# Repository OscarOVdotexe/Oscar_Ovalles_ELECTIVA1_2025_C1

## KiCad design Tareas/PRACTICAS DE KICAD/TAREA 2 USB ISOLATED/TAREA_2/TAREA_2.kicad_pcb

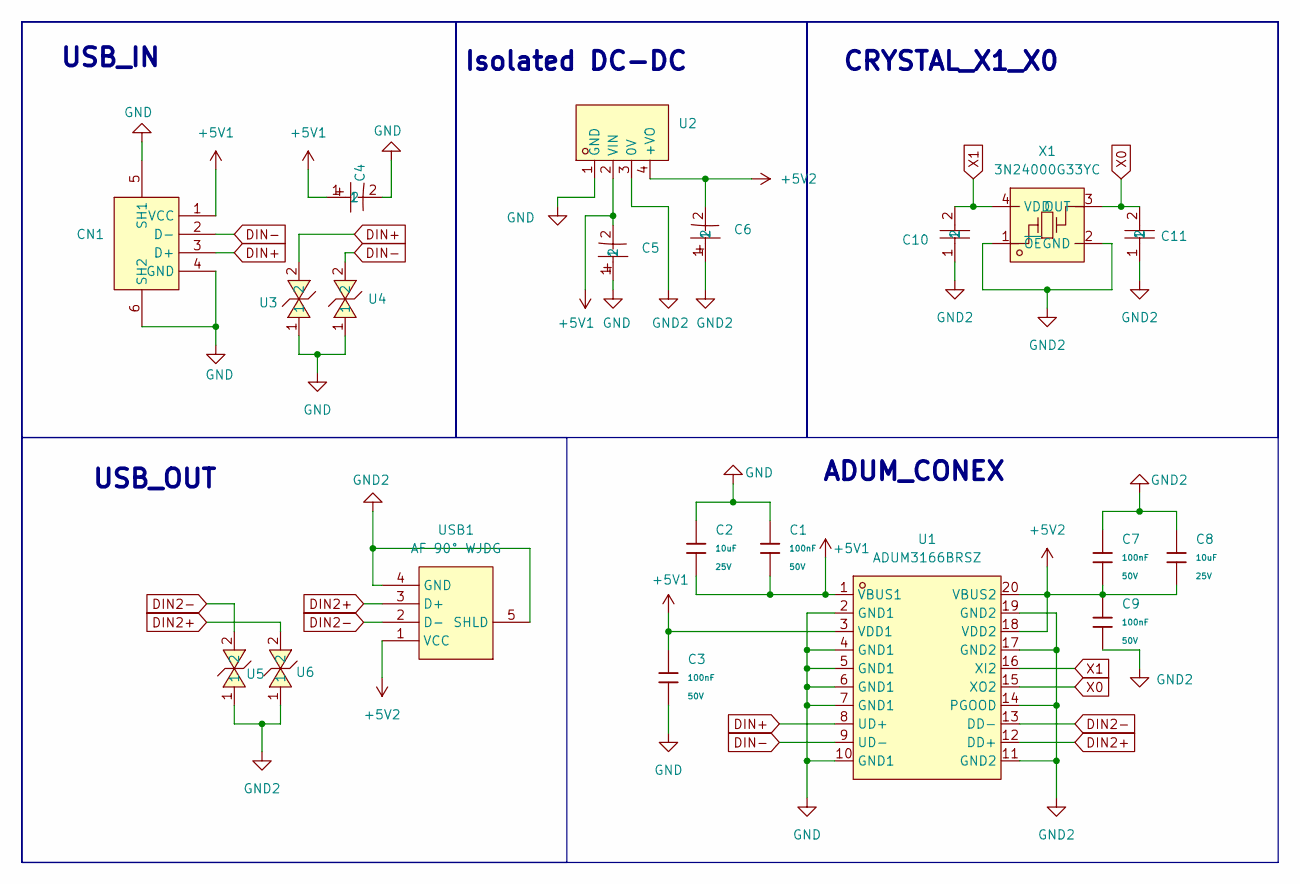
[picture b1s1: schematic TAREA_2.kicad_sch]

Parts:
C1, C3, C7, C9: 100nF; C_0603; Voltage Rated 50V; Tolerance ±10%; Part CC0603KRX7R9BB104; LCSC C14663
C2, C8: 10uF; C_0805; Voltage Rated 25V; Tolerance ±10%; Part CL21A106KAYNNNE; LCSC C15850
C4, C5, C6: 4.7uF 25V 3*5; CAP-TH_BD4.0-P1.50-D0.8-FD; LCSC Part C44582
C10, C11: 0805CG8R0C500NT; C0805; LCSC Part C1839
CN1: USB-B-Female-90; USB-B_TH_USB-B-FEMALE-90; LCSC Part C46392
U1: ADUM3166BRSZ; SSOP-20_L7.2-W5.3-P0.65-LS7.8-BL; LCSC Part C7453661
U2: B0503S-1WR3_C5444000; PWRM-TH_B0503S-1WR2; LCSC Part C5444000
U3, U4, U5, U6: TVSS5VCES-02GP-J_C7473318; SOD-523_L1.2-W0.8-LS1.6-BI; LCSC Part C7473318
USB1: AF 90° WJDG; USB-A-TH_AF-WJDG; LCSC Part C456018
X1: 3N24000G33YC; OSC-SMD_4P-L3.2-W2.5-BL; LCSC Part C252339

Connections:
+5V1: C1.1, C2.2, C3.2, C4.1, C5.2, CN1.1 (VCC), U1.1 (VBUS1), U1.3 (VDD1), U2.2 (VIN)
+5V2: C6.2, C7.1, C8.2, C9.2, U1.18 (VDD2), U1.20 (VBUS2), U2.4 (+VO), USB1.1 (VCC)
DIN2+: U1.12 (DD+), U6.2, USB1.3 (D+)
DIN2-: U1.13 (DD−), U5.2, USB1.2 (D-)
DIN+: CN1.3 (D+), U1.8 (UD+), U3.2
DIN-: CN1.2 (D-), U1.9 (UD−), U4.2
GND: C1.2, C2.1, C3.1, C4.2, C5.1, CN1.4 (GND), CN1.5 (SH1), CN1.6 (SH2), U1.2 (GND1), U1.4 (GND1), U1.5 (GND1), U1.6 (GND1), U1.7 (GND1), U1.10 (GND1), U2.1 (GND), U3.1, U4.1
GND2: C6.1, C7.2, C8.1, C9.1, C10.1, C11.1, U1.11 (GND2), U1.14 (PGOOD), U1.17 (GND2), U1.19 (GND2), U2.3 (0V), U5.1, U6.1, USB1.4 (GND), USB1.5 (SHLD), X1.1 (~OE), X1.2 (GND)
X0: C11.2, U1.15 (XO2), X1.3 (OUT)
X1: C10.2, U1.16 (XI2), X1.4 (VDD)

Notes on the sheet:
Isolated DC-DC
USB_OUT
USB_IN
CRYSTAL_X1_X0
ADUM_CONEX

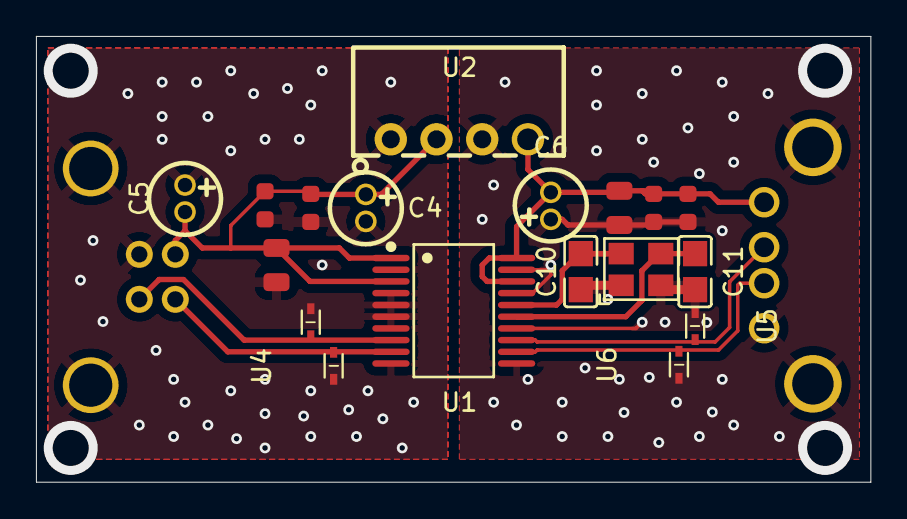
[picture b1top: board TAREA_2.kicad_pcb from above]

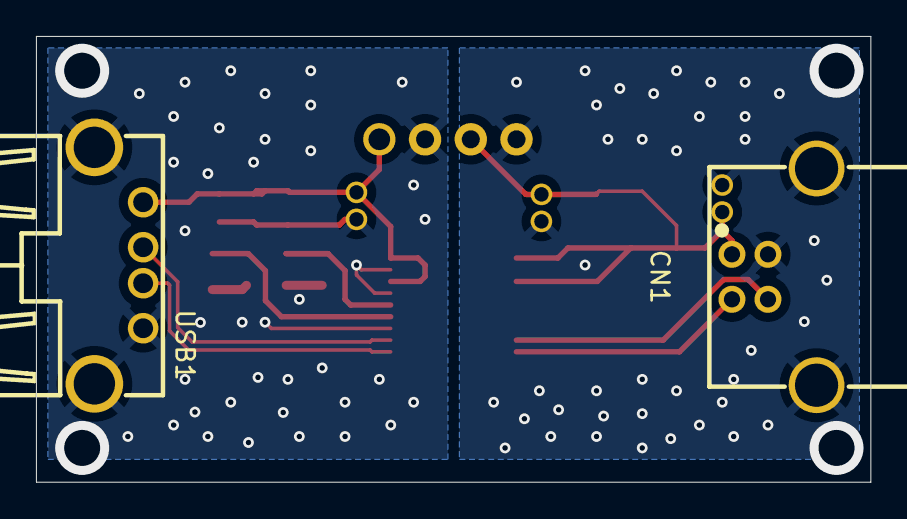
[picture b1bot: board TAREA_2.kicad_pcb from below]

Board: 2 copper layers, 46.4 x 24.8 mm, 20 parts (2 on the bottom side), 10 nets.

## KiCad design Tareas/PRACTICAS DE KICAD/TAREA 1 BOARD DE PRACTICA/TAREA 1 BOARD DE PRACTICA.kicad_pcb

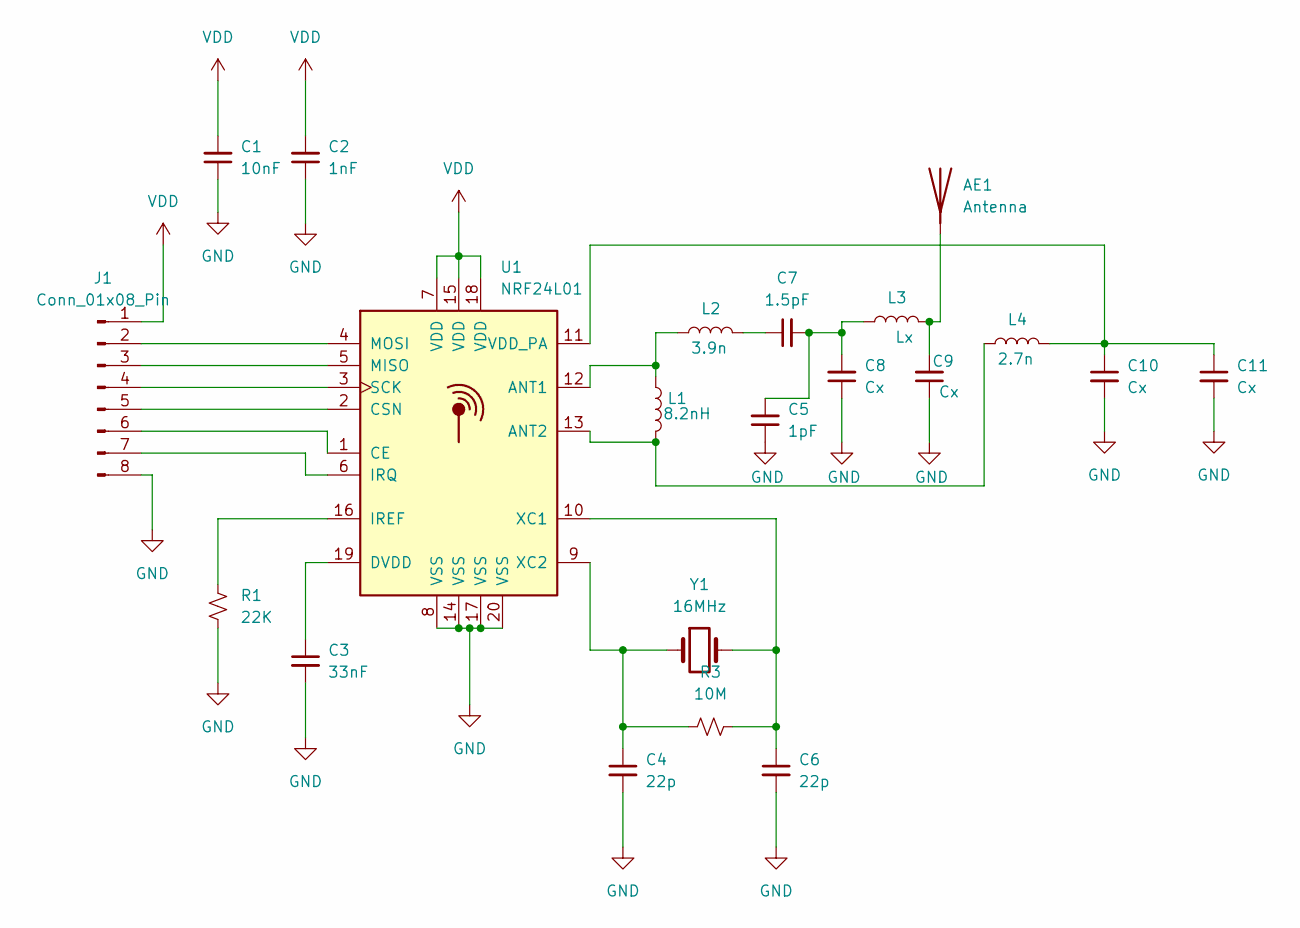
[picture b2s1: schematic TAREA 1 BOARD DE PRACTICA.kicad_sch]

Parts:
AE1: Antenna; Texas_SWRA117D_2.4GHz_Right
C1: 10nF; C_0402_1005Metric
C2: 1nF; C_0402_1005Metric
C3: 33nF; C_0402_1005Metric
C4, C6: 22p; C_0402_1005Metric
C5: 1pF; C_0402_1005Metric
C7: 1.5pF; C_0402_1005Metric
C8, C9, C10, C11: Cx; C_0402_1005Metric
J1: Conn_01x08_Pin; Hirose_DF13-08P-1.25DSA_1x08_P1.25mm_Vertical
L1: 8.2nH; L_0402_1005Metric
L2: 3.9n; L_0402_1005Metric
L3: Lx; L_0402_1005Metric
L4: 2.7n; L_0402_1005Metric
R1: 22K; R_0402_1005Metric
R3: 10M; R_0402_1005Metric
U1: NRF24L01; QFN-20-1EP_4x4mm_P0.5mm_EP2.5x2.5mm
Y1: 16MHz; Crystal_SMD_3215-2Pin_3.2x1.5mm

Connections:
GND: C1.1, C2.1, C3.2, C4.2, C5.1, C6.2, C8.1, C9.1, C10.2, C11.2, J1.8, R1.2, U1.8 (VSS), U1.14 (VSS), U1.17 (VSS), U1.20 (VSS)
unnamed: AE1.1 (A), C9.2, L3.2
unnamed: C5.2, C7.2, C8.2, L3.1
unnamed: C7.1, L2.2
unnamed: J1.2, U1.4 (MOSI)
unnamed: J1.3, U1.5 (MISO)
unnamed: J1.4, U1.3 (SCK)
unnamed: J1.5, U1.2 (CSN)
unnamed: J1.6, U1.1 (CE)
unnamed: J1.7, U1.6 (IRQ)
unnamed: L1.1, L2.1, U1.12 (ANT1)
unnamed: L1.2, L4.1, U1.13 (ANT2)
unnamed: C3.1, U1.19 (DVDD)
unnamed: R1.1, U1.16 (IREF)
unnamed: C10.1, C11.1, L4.2, U1.11 (VDD_PA)
unnamed: C6.1, R3.2, U1.10 (XC1), Y1.2
unnamed: C4.1, R3.1, U1.9 (XC2), Y1.1
VDD: C1.2, C2.2, J1.1, U1.7 (VDD), U1.15 (VDD), U1.18 (VDD)

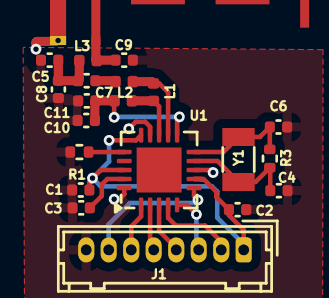
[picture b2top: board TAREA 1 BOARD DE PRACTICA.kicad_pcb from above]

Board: 2 copper layers, 21 parts (0 on the bottom side), 18 nets.

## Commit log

2025-01-19 dalepaya 1
2025-01-19 Create pruebita
2025-01-19 commiutendo archivos
2025-01-19 nuevo commit local
2025-01-20 mitarea
2025-04-04 last update t2
2025-04-05 LAST UPDATE 5/4/25
    USB TERMINADO
2025-04-25 LAST UPDATE
2025-04-25 LAST
